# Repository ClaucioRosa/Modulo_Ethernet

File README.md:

# Modulo_Ethernet
## Modulo Ethernet - Hardware 

## Descrição
O Módulo Ethernet é utilizado para atribuir aos microcontroladores a conexão ethernet / internet, tornando possível controlá-los a partir da rede interna (ethernet) ou através da rede externa (internet). 
Muitos projetos desenvolvidos com microcontroladores necessitam de acesso / controle de forma remota e ao utilizar o Módulo Ethernet essa necessidade é suprida de forma simples e prática, pois basta fazer as ligações entre o módulo e o microcontrolador, conectar o módulo ao roteador através de um cabo de rede com RJ45, inserir o código fonte correto no microcontrolador e usufruir dos benefícios.

Ao inserir o microcontrolador na internet, você pode acessá-lo de qualquer local do mundo, seja com um computador, smartphone ou tablet e obter informações ou solicitar que ações sejam executadas. Para projetos que envolvam integração entre o microcontrolador e aplicações Android ou iOS, o Módulo Ethernet se torna um membro importante do projeto.

## – Especificações e características:

#### – Controlador: ENC28J60
#### – Tensão de operação: 3,3VDC
#### – Velocidade de conexão: 10 / 100Mb
#### – Protocolos Suportados: TCP / IP
#### – Conexão com o Arduino através de SPI
#### – Possui cristal oscilador de 25MHz

https://ww1.microchip.com/downloads/en/DeviceDoc/39662c.pdf

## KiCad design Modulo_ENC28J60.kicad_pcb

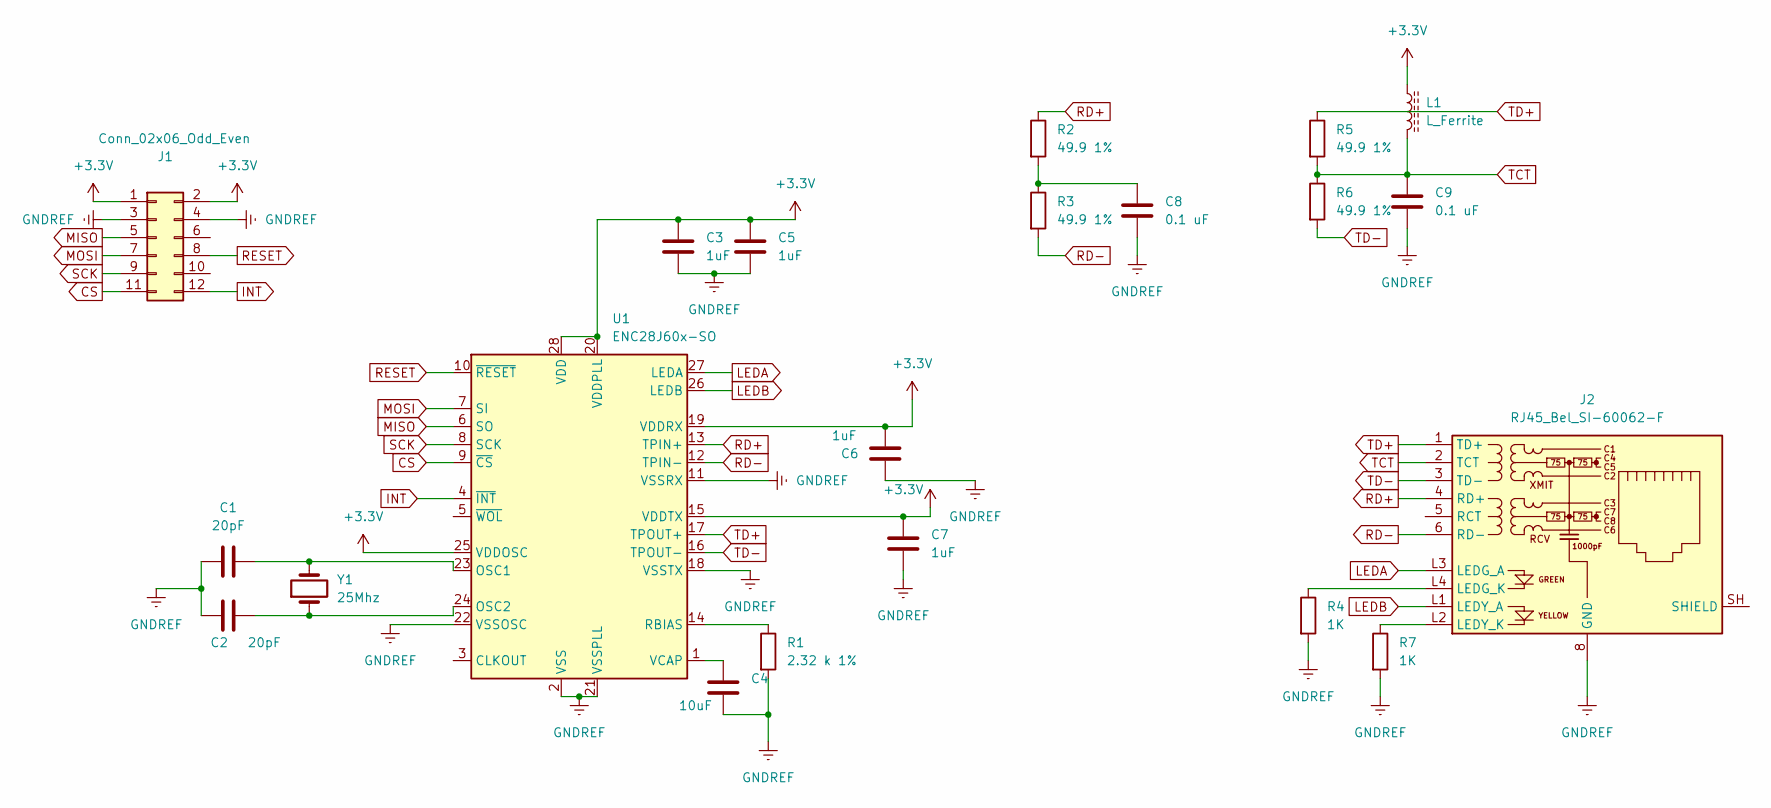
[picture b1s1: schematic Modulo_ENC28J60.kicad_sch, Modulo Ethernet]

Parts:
C1, C2: 20pF; R_1210_3225Metric_Pad1.30x2.65mm_HandSolder
C3, C5, C6, C7: 1uF; R_1210_3225Metric_Pad1.30x2.65mm_HandSolder
C4: 10uF; R_1210_3225Metric_Pad1.30x2.65mm_HandSolder
C8, C9: 0.1 uF; R_1210_3225Metric_Pad1.30x2.65mm_HandSolder
J1: Conn_02x06_Odd_Even; PinHeader_2x06_P1.27mm_Vertical
J2: RJ45_Bel_SI-60062-F
L1: L_Ferrite; R_1206_3216Metric_Pad1.30x1.75mm_HandSolder
R1: 2.32 k 1%; R_1210_3225Metric_Pad1.30x2.65mm_HandSolder
R2, R3, R5, R6: 49.9 1%; R_1210_3225Metric_Pad1.30x2.65mm_HandSolder
R4, R7: 1K; R_1210_3225Metric_Pad1.30x2.65mm_HandSolder
U1: ENC28J60x-SO; SOIC-28W_7.5x17.9mm_P1.27mm
Y1: 25Mhz; Crystal_HC49-4H_Vertical

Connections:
+3.3V: C3.1, C5.1, C6.1, C7.1, J1.1, J1.2, L1.1, U1.15 (VDDTX), U1.19 (VDDRX), U1.20 (VDDPLL), U1.25 (VDDOSC), U1.28 (VDD)
CS: J1.11, U1.9 (~CS)
GNDREF: C1.1, C2.1, C3.2, C4.2, C5.2, C6.2, C7.2, C8.2, C9.2, J1.3, J1.4, J2.8 (GND), R1.2, R4.2, R7.2, U1.2 (VSS), U1.11 (VSSRX), U1.18 (VSSTX), U1.21 (VSSPLL), U1.22 (VSSOSC)
INT: J1.12, U1.4 (~INT)
LEDA: J2.L3 (LEDG_A), U1.27 (LEDA)
LEDB: J2.L1 (LEDY_A), U1.26 (LEDB)
MISO: J1.5, U1.6 (SO)
MOSI: J1.7, U1.7 (SI)
unnamed: C1.2, U1.23 (OSC1), Y1.2
unnamed: C2.2, U1.24 (OSC2), Y1.1
unnamed: C4.1, U1.1 (VCAP)
unnamed: C8.1, R2.2, R3.1
unnamed: J2.L2 (LEDY_K), R7.1
unnamed: J2.L4 (LEDG_K), R4.1
unnamed: R1.1, U1.14 (RBIAS)
RD+: J2.4 (RD+), R2.1, U1.13 (TPIN+)
RD-: J2.6 (RD-), R3.2, U1.12 (TPIN-)
RESET: J1.8, U1.10 (~RESET)
SCK: J1.9, U1.8 (SCK)
TCT: C9.1, J2.2 (TCT), L1.2, R5.2, R6.1
TD+: J2.1 (TD+), R5.1, U1.17 (TPOUT+)
TD-: J2.3 (TD-), R6.2, U1.16 (TPOUT-)

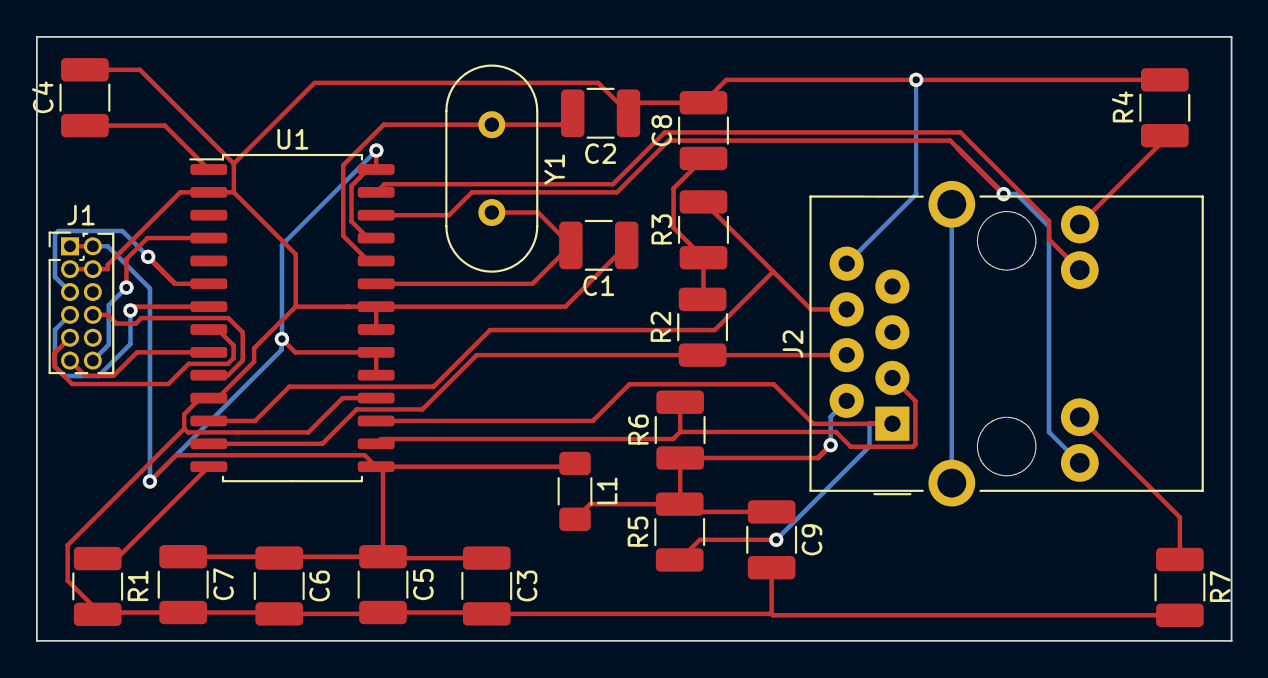
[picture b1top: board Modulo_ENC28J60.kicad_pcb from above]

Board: 2 copper layers, 66.4 x 33.6 mm, 21 parts (0 on the bottom side), 22 nets.

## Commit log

2023-04-22 Arquivos Kicad 6
2024-06-09 Add files via upload
    Atualização do conector Rj45
2025-08-24 arquivo txt
2025-08-25 Roteamento de trilhas
2025-09-16 Roteamento Trilhas
